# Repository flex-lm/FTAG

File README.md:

# FTAG
This is a simple USB to Jtag, SPI and RS232 interface for experimental and research usage that's based around the FTDI FT232H.

This circuit has experimental and dangerous features! Build at your own risk!

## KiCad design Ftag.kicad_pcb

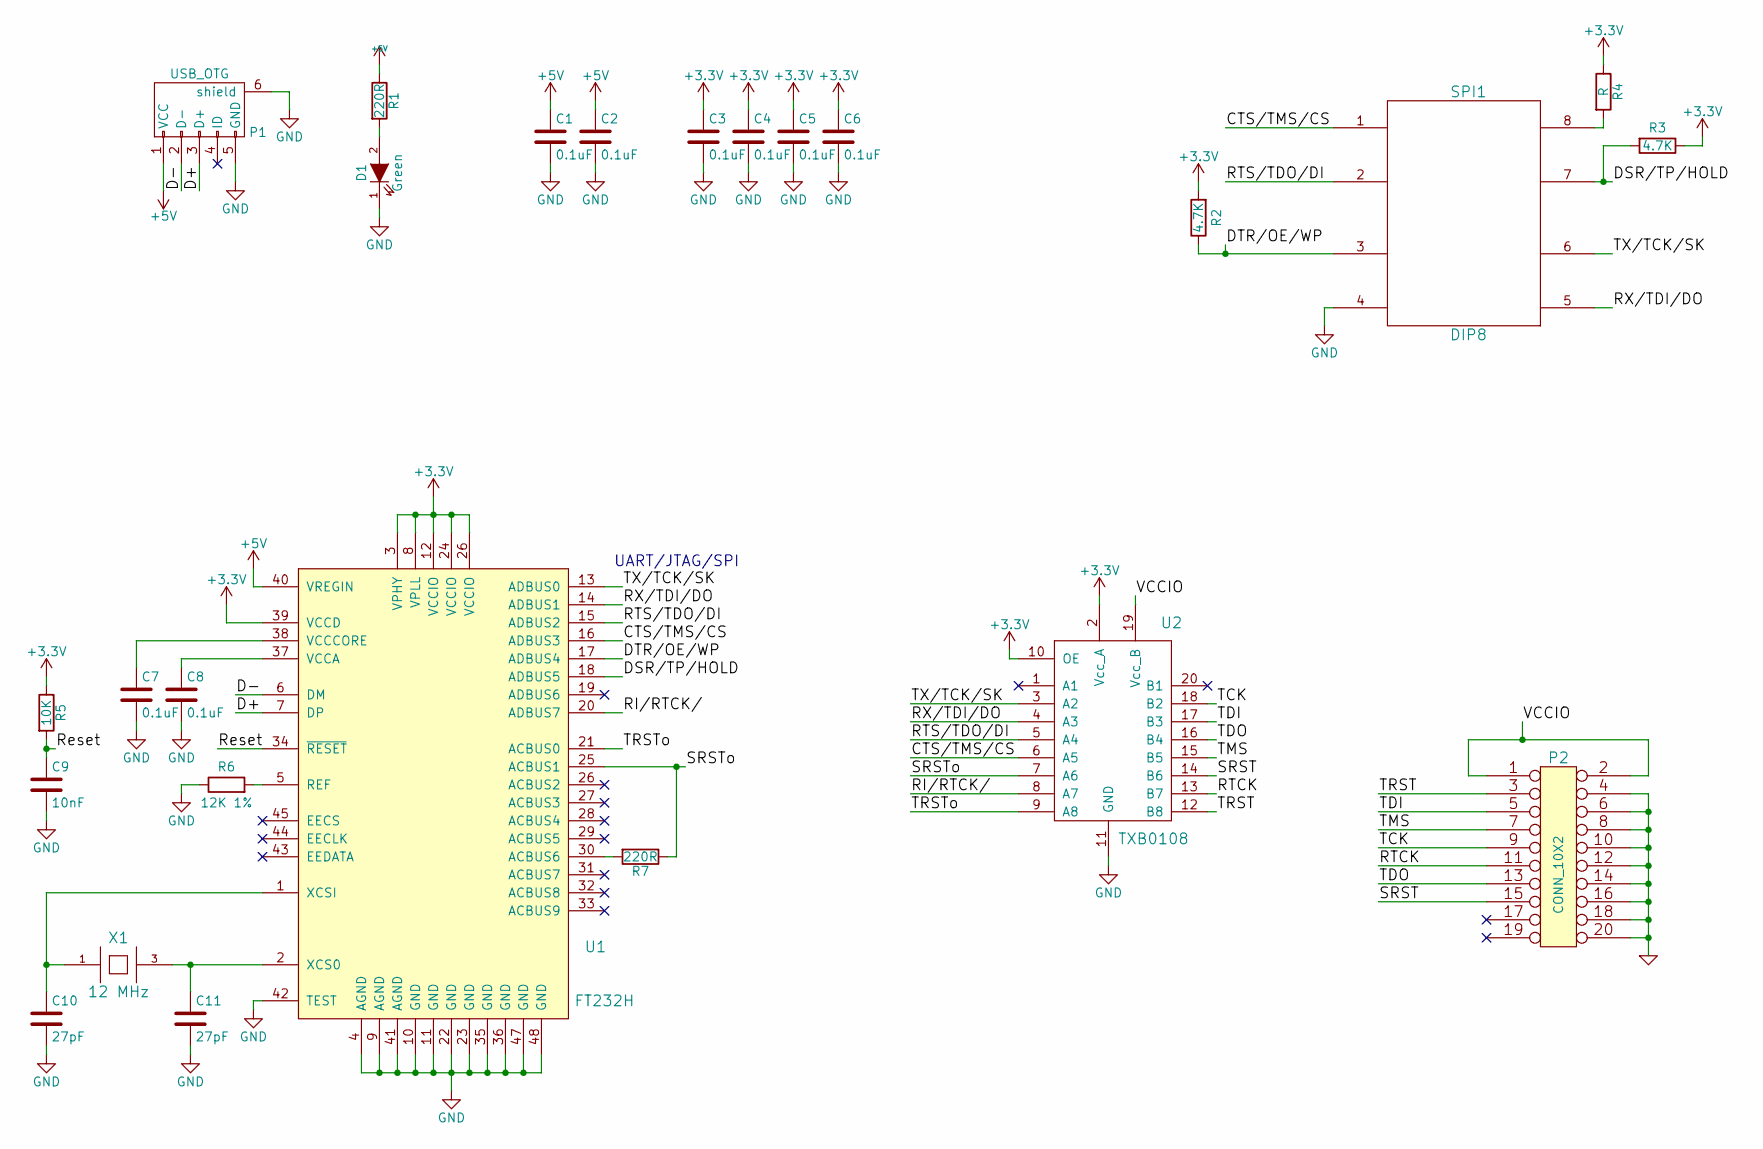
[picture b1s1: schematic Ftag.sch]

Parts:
C1, C2, C3, C4, C5, C6, C7, C8: 0.1uF; C_0603_HandSoldering
C9: 10nF; C_0603_HandSoldering
C10, C11: 27pF; C_0603_HandSoldering
D1: Green; LED_0805
P1: USB_OTG; USB_Micro-B
P2: CONN_10X2; IDC_Header_Straight_20pins
R1, R7: 220R; R_0603_HandSoldering
R2, R3: 4.7K; R_0603_HandSoldering
R4: R; R_0603_HandSoldering
R5: 10K; R_0603_HandSoldering
R6: 12K 1%; R_0603_HandSoldering
SPI1: DIP8; DIP-8_W7.62mm_LongPads
U1: FT232H; LQFP-48_7x7mm_Pitch0.5mm
U2: TXB0108; SSOP-20_4.4x6.5mm_Pitch0.65mm
X1: 12 MHz; Q_49U3HMS

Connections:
+3V3: C3.1, C4.1, C5.1, C6.1, R2.2, R3.1, R4.1, R5.1, U1.3 (VPHY), U1.8 (VPLL), U1.12 (VCCIO), U1.24 (VCCIO), U1.26 (ACBUS2), U1.39 (VCCD), U2.2 (Vcc_A), U2.10 (OE)
+5V: C1.1, C2.1, P1.1 (VCC), R1.1, U1.40 (VREGIN)
/CTS/TMS/CS: SPI1.1, U1.16 (ADBUS3), U2.6 (A5)
/D+: P1.3 (D+), U1.7 (DP)
/D-: P1.2 (D-), U1.6 (DM)
/DSR/TP/HOLD: R3.2, SPI1.7, U1.18 (ADBUS5)
/DTR/OE/WP: R2.1, SPI1.3, U1.17 (ADBUS4)
/RI/RTCK/: U1.20 (ADBUS7), U2.8 (A7)
/RTCK: P2.11, U2.13 (B7)
/RTS/TDO/DI: SPI1.2, U1.15 (ADBUS2), U2.5 (A4)
/RX/TDI/DO: SPI1.5, U1.14 (ADBUS1), U2.4 (A3)
/Reset: C9.1, R5.2, U1.34 (~RESET)
/SRST: P2.15, U2.14 (B6)
/SRSTo: R7.1, U1.25 (ACBUS1), U2.7 (A6)
/TCK: P2.9, U2.18 (B2)
/TDI: P2.5, U2.17 (B3)
/TDO: P2.13, U2.16 (B4)
/TMS: P2.7, U2.15 (B5)
/TRST: P2.3, U2.12 (B8)
/TRSTo: U1.21 (ACBUS0), U2.9 (A8)
/TX/TCK/SK: SPI1.6, U1.13 (ADBUS0), U2.3 (A2)
/VCCIO: P2.1, P2.2, U2.19 (Vcc_B)
GND: C1.2, C2.2, C3.2, C4.2, C5.2, C6.2, C7.2, C8.2, C9.2, C10.2, C11.2, D1.1 (K), P1.5 (GND), P1.6 (shield), P2.4, P2.6, P2.8, P2.10, P2.12, P2.14, P2.16, P2.18, P2.20, R6.1, SPI1.4, U1.4 (AGND), U1.9 (AGND), U1.10 (GND), U1.11 (GND), U1.22 (GND), U1.23 (GND), U1.35 (GND), U1.36 (GND), U1.41 (AGND), U1.42 (TEST), U1.47 (GND), U1.48 (GND), U2.11 (GND)
unnamed: C7.1, U1.38 (VCCCORE)
unnamed: C8.1, U1.37 (VCCA)
unnamed: C10.1, U1.1 (XCSI), X1.1
unnamed: C11.1, U1.2 (XCS0), X1.3
unnamed: D1.2 (A), R1.2
unnamed: R4.2, SPI1.8
unnamed: R6.2, U1.5 (REF)
unnamed: R7.2, U1.30 (ACBUS6)

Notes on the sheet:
UART/JTAG/SPI

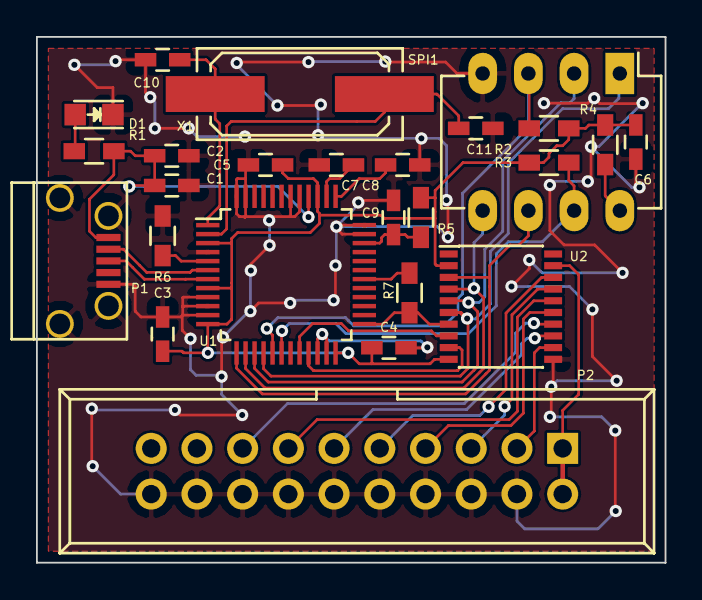
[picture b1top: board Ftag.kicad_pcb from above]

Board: 2 copper layers, 34.9 x 29.2 mm, 25 parts (0 on the bottom side), 31 nets.

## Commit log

2015-09-12 Lets hack embedded devices!
2015-09-13 Added note about experimental feature
2015-09-13 Added pictures of the board
2015-09-16 Updated pictures
2015-11-27 removed experimental parts
2015-12-07 Added output buffer
    Some things still have to be checked before adding part footprints
2016-06-10 Changed buffer and updated schematic
2016-07-19 Assigned component footprints
2016-07-20 Started board layout
2016-07-20 Added some routing
2016-07-21 Finished preliminary layout
2016-07-22 Added via stitching
2016-07-22 Added silkscreen pinout
2016-07-23 Finished PCB layout
